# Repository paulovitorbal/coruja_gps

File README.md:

# coruja_gps — detector de radares embarcado

Projeto pessoal de estudo em sistemas embarcados: um alertador de radares e semáforos
sobre **Raspberry Pi Pico 2 W**, com firmware em **C++17 / Pico SDK**.

Lê telemetria de um GPS NEO-M8N por UART, confronta a posição com uma base local de
18.294 pontos e sinaliza em quatro zonas por display, LED RGB periférico e buzzer.

## Arquitetura

Quatro subsistemas, e o dado atravessa todos eles. Um CSV vira `radares.bin` na
estação de trabalho; o binário é publicado por um servidor mínimo; a configuração vai
para o cartão à mão; e o aparelho, ao clique, lê o cartão, busca a base pela rede e
**a grava de volta no cartão**.

Essa última parte é o RF05: *"baixá-la e salvá-la no cartão"*, com a troca atômica do
RF05.2 — baixa para `radares.tmp`, valida, renomeia a atual para `radares.bak` e só
então promove a nova. Queda de energia no meio de uma atualização não pode deixar o
aparelho sem base, porque a tela voltaria ao velocímetro normalmente e nada indicaria
a perda.

A cópia do `radares.bin` para o cartão à mão é só a **carga inicial**, e é opcional:
sem base o aparelho sobe, avisa, e o primeiro clique busca tudo pela rede.

No boot a base é lida **em fluxo** do cartão, decodificando direto no vetor de pontos.
Não é preferência de estilo: o arquivo tem 214 KB e o vetor ocupa 281 KB, e não existe
instante em que os dois caibam nos 181 KiB livres. Se o `radares.bin` não validar, o
firmware cai para o `radares.bak` — e avisa que está operando pela reserva.

**De onde vem o CSV é problema de quem monta** — o projeto não presume fonte nenhuma,
e por isso ela aparece no diagrama como uma nuvem anônima.

O que ainda não existe está tracejado e em cinza: gravar no cartão o que foi baixado,
o GPS, o display e o buzzer.

### Dentro do firmware

A divisão que mais importa é a **fronteira do hardware**. Em verde, o que compila e é
testado no host — validação de formato, decodificação de quadratura, verificação de
download, análise de URL. São 180 testes que rodam sem placa nenhuma, e é o que torna
possível trabalhar neste projeto enquanto um módulo não chegou pelo correio.

Em laranja, o que só existe no Pico. Esses módulos são finos de propósito: o
`ClienteHttp` entrega pedaços a quem chamou em vez de acumular, e quem verifica é o
`nucleo`.

### Como regerar os diagramas

As fontes são versionadas em `docs/*.puml`; os SVG são gerados.

```bash
plantuml -tsvg docs/arquitetura.puml docs/firmware.puml
```

## Base de pontos

O firmware carrega `radares.bin`, um binário compacto de 12 bytes por ponto,
ordenado por latitude. Ele é produzido por `converte.py` a partir de um CSV no
**padrão iGO8**:

```
X,Y,TYPE,SPEED,DirType,Direction
-44.021044,-19.799916,1,30,1,257
```

```bash
python3 converte.py base_igo8.txt radares.bin
```

**Outro formato de entrada?** Escreva seu próprio parser — e não reimplemente o
formato binário. `formato_radares.py` expõe as enumerações e o escritor:

```python
from formato_radares import Ponto, TipoPonto, Sentido, escreve

pontos = [Ponto(lat=-19.799916, lon=-44.021044, limite=30, rumo=257,
                tipo=TipoPonto.RADAR_FIXO, sentido=Sentido.UNIDIRECIONAL)]
escreve(pontos, "radares.bin")
```

O `escreve()` cuida de quantização, flags, **ordenação por latitude** e CRC-32 — as
quatro coisas que um parser erraria em silêncio. A ordenação é a pior: a busca
binária do firmware depende dela e erra *sem avisar* se faltar.

Para testar, `formato_radares.le()` relê com as mesmas validações do firmware: se
aceita, o firmware carrega. Use `converte.py` (padrão iGO8) como modelo.

Obter a base é problema de quem monta: o projeto não presume fonte nenhuma.

---

## Alimentação e instalação no veículo

Alimentado pelo **pós-chave**, derivado na caixa de fusíveis. **O que entra no aparelho
é 12 V** — o conversor CC ficou para dentro.

Essa topologia mudou em 2026-09-21, e o motivo foi o buzzer. Ver `docs/adr/0009`.

```
bateria ─ caixa de fusíveis ─ piggyback ─ fusível 2 A ─ 1,5 mm² trançado (12 V)
                                                               │
                                              ┌────────────────▼──────────────┐
                                              │  conector de entrada, 3 vias  │
                                              └────────────────┬──────────────┘
                                                               │  dentro do gabinete
                                     ┌─────────────────────────┼───────────────┐
                                     │                         │               │
                          ┌──────────▼──────────┐   ┌──────────▼─────────┐     │
                          │ TVS 24 V ┬ 470 µF   │   │ conversor 12 V→5 V │     │
                          │ (bidir.) │ 50 V     │   │ NÃO isolado, ≥40 V │     │
                          └──────────┴──────────┘   └──────────┬─────────┘     │
                                                               │ 5 V           │ 12 V
                                                    ┌──────────▼─────────┐  ┌──▼──────────┐
                                                    │ Schottky → VSYS 39 │  │ buzzer, 2 v.│
                                                    └────────────────────┘  └─────────────┘
```

Consumo: **~145 mA em 12 V** (≈1,6 W) em condução normal, com pico de ~200 mA quando a
tensão cai a 9 V durante a partida. No lado de 5 V são ~162 mA normais e ~310 mA no
pior caso sustentado.

### O buzzer é alimentado em 12 V

O **SFM-20B é especificado para 3–24 V**. Em 5 V ele opera perto do mínimo da faixa; em
12 V, perto do meio — e para um piezo ativo a pressão sonora sobe bastante com a
tensão. O **R-32** registra a audibilidade com janelas abertas a 80 km/h como a
incerteza que sobrou do projeto, e nenhuma mudança de firmware a resolve. Esta resolve,
ou pelo menos ataca a causa certa.

O circuito não muda: o `BC337` tem `Vceo` de 45 V, a corrente é a mesma, e o
acionamento pela base continua em 3,3 V através de 1 kΩ. Não há roda-livre a
acrescentar — o buzzer é piezoelétrico, carga capacitiva.

**O `D2` foi removido em 2026-09-25**, justamente por isso: em antiparalelo com carga
capacitiva ele fica reversamente polarizado nos dois estados e nunca conduz. Fecha o
R-16.

O retorno do buzzer não vai ao GND por fio — vai **pelo transistor**. É chaveamento
pelo lado baixo: `+12 V → buzzer → coletor`, `emissor → GND`. Com o `Q1` cortado o
coletor sobe a ~12 V pelo próprio buzzer, que é por que, lendo a netlist parada, as
duas pernas parecem estar no mesmo potencial.

### 🔴 O 12 V agora está dentro do gabinete

Essa é a contrapartida, e é séria.

Antes, com o conversor do lado de fora, nada acima de 5 V entrava na caixa. Agora
entram 12 V, e eles convivem a centímetros de um trilho cujo máximo absoluto é 5,5 V.
**12 V no nó `VSYS` destrói Pico, GPS, display e cartão juntos.**

Três consequências práticas:

* **O conector de entrada tem 3 vias e o do buzzer tem 2**, e isso voltou a ser medida
  de **segurança**, não de robustez. A revisão anterior deste documento dizia que
  trocá-los "deixou de ser destrutivo" — aquilo valia enquanto só havia 5 V; não vale
  mais.
* **O fio de 12 V não é vermelho.** A convenção antiga mandava vermelho para 5 V *e*
  12 V; duas tensões com a mesma cor a três centímetros uma da outra é convite a erro.
  No `.fzz` o 12 V é **amarelo**.
* **O fio do coletor também está em 12 V** sempre que o transistor está cortado, ou
  seja, na maior parte do tempo. Não é só o `+12 V` que precisa de cuidado.

### Proteção da entrada de 12 V

O fusível protege o **fio** contra curto; ele não reage a sobretensão. Daí o **TVS
bidirecional de 24 V** (`P6KE24CA` ou `1.5KE24CA`) e um **eletrolítico de 470 µF /
50 V** em paralelo na entrada. O clamp de 24 V cai numa janela estreita: tem de ficar
acima de 16 V, porque a rede é 13,8 a 14,4 V com o motor ligado, e abaixo de 40 V,
porque é o máximo do conversor. O `24CA` clampa em 33,2 V.

**O que isso não resolve:** um *load dump* real chega a 60–120 V por até 400 ms, o que
contra um clamp de 33 V significa mais de 1 kW sustentado — nenhum TVS axial pequeno
sobrevive. O que ele cobre são os transientes frequentes e de baixa energia, que são os
que matam módulo barato no uso diário. Para o load dump, o projeto se apoia em o
alternador de carro moderno já clampar internamente em ~35 V, e isso é **suposição, não
medição**.

Dois detalhes que estragam tudo se errados: o sufixo **`CA`** significa bidirecional, e
a versão `A` montada ao contrário fica em curto permanente; e o **fusível vai antes** da
proteção no percurso do cabo, porque o modo de falha desejável de um TVS é curto.

### Três decisões que não são óbvias

**Pós-chave em vez de bateria direta com relé.** O pós-chave permanece energizado
durante a partida, então não há reinício na ignição. O relé foi descartado porque a
bobina consome 80–150 mA contra ~180 mA do aparelho inteiro — gastaria quase tanto
quanto liga — e o benefício dele (consumo parasita zero) já vem da chave de ignição.

**Fusível de 2 A, não 10 A.** Fusível protege o fio, não a carga. Com 10 A, uma falta
intermediária de 6 A não abriria o fusível mas aqueceria o condutor. O cabo de 1,5 mm²
suporta ~15 A e está sobredimensionado de propósito — mas o fusível acompanha a carga.

**Conversor não isolado, com entrada ≥ 40 V.** As duas condições importam por motivos
diferentes. A entrada ampla é pelo *load dump*: 60–120 V por dezenas de milissegundos
quando a carga do alternador sai, e módulos comuns de 35 V podem não sobreviver. O
**não isolado** é pelo buzzer: sem continuidade entre o negativo de 12 V e o do
aparelho, a corrente do buzzer não fecha pelo emissor do `Q1` e ele simplesmente não
toca. Um conversor isolado — que parece melhor no anúncio — quebraria o circuito.

E há um mínimo tão importante quanto o máximo: **a entrada tem de aceitar ~9 V**,
porque é onde o trilho cai durante a partida. Módulo com mínimo de 12 V reinicia o
aparelho a cada vez que se dá a chave.

### Ajuste opcional da saída do conversor

O Schottky derruba 0,3–0,45 V, então 5,00 V na saída deixam o `VSYS` em ~4,6 V. Se o
módulo for ajustável, regule para **5,35–5,45 V** e o `VSYS` chega a ~5,0 V. **Nunca
acima de 5,8 V** — o `VSYS` aceita no máximo 5,5 V. Meça antes de conectar.

Com o buzzer em 12 V isso deixou de ser crítico: o que dependia de tensão nominal saiu
do trilho de 5 V.

### Conectores do aparelho

| Conector | Vias | Pino A | Pino B |
| :--- | :---: | :--- | :--- |
| Entrada (único) | **3** (central sem uso) | **+12 V** | GND |

Desde 2026-09-25 o **buzzer é soldado direto**, sem conector: os dois fios saem da
placa e vão ao SFM-27 no painel da caixa. Com isso o aparelho tem **um só conector
externo**, e o risco de trocar um pelo outro — que a contagem de vias apenas
administrava — deixa de existir. O preço é serviço: separar a tampa exige dessoldar.

## Documentos

Leia nesta ordem:

| Documento | O que é |
| :--- | :--- |
| **`requirements.md`** | Requisitos funcionais e não-funcionais, matriz de interação homem-máquina e fluxo de telas. É a especificação. |
| **`bom_schematic.md`** | Lista de materiais e roteamento pino a pino, com as pinagens físicas conferidas nas placas. |
| **`formato_dados.md`** | Formato binário `radares.bin`, estratégia de carga em RAM e busca geográfica em dois estágios. |
| **`revisao_tecnica.md`** | Revisão técnica com rastreabilidade: o que foi achado, decidido e o que segue aberto. |
| **`montagem.md`** | Montagem física na caixa Patola PB-111: chassi, fixação, prateleira do GPS, isolamento e passagem de cabos. |
| **`previa_host.md`** | O produto inteiro rodando no host contra o simulador: o que a primeira integração validou, o defeito que achou e o que ela ainda não exercita. |
| **`roteiro_bancada.html`** | Procedimento de medição para imprimir, com quadro de registro das leituras. |

## Estado

**Decidido:** C++17 com Pico SDK · GPS+GLONASS a 4 Hz (piso 3 Hz) · conector JST-XH ·
GPS alimentado em 5 V · Zona de Semáforo silenciosa · buzzer escalonado em 3 faixas ·
LED RGB exclusivo de estado de via.

**Pendente de bancada** — ver `roteiro_bancada.html`:

| Item | Medida |
| :--- | :--- |
| R-05 | Vf dos LEDs verde e azul, e calibração das razões R:G (amarelo) e R:B (rosa) |
| R-13 | Tensão do trilho 3V3 sob carga, com backlight em 100% |
| R-17 | Consumo do buzzer e pinagem do transistor |
| R-14 | Inspeção: regulador de 3 pinos na placa GPS — **sem ele, 5 V destroem o módulo** |

**Escopo futuro:** desenho de telas e interfaces visuais.

## Esquemático no Fritzing

`coruja_gps.fzz` foi **gerado** e depois **ajustado à mão** no Fritzing:

```bash
python3 gera_fritzing.py    # ⚠️ sobrescreve o .fzz e DESCARTA o ajuste manual
```

> ⚠️ **O `.fzz` versionado contém trabalho manual que o gerador não reproduz:**
> roteamento dos fios com pontos de dobra, orientação de 16 peças e 4 notas rotulando
> os módulos representados por headers genéricos. Regerar descarta tudo isso.
>
> O gerador é a fonte da **netlist**; o `.fzz` é a fonte do **layout**. Ao mudar a
> fiação, o caminho é editar `NETS`, regerar num arquivo temporário, comparar as redes
> e então aplicar a mudança à mão no Fritzing — não sobrescrever.
>
> **Sem divergências conhecidas** (2026-09-21). O `.fzz` foi regerado a partir da
> netlist atual e depois roteado à mão, fechando o **R-29**.
>
> O anterior tinha acumulado cinco atrasos, e o pior era silencioso: ele trazia o LED
> como **cátodo comum**, que se liga de forma oposta ao ânodo comum real (R-33). Quem
> montasse por ele teria um LED que não acende, sem pista do motivo. Os outros quatro
> eram os GPIO de vermelho e azul trocados (R-35), resistores de 68 Ω onde as medições
> pediam 470 e 150 (R-05), leitor SD com 8 pinos em vez de 9 (R-40) e o display como
> ST7789 240×240.
>
> A lição que fica: um `.fzz` editado à mão **não avisa quando envelhece**. A defesa
> aqui foi comparar netlists entre o gerado e o versionado — vale repetir isso antes de
> cada montagem, e não confiar na memória de quantas correções entraram desde a última
> vez. O documento de referência para montagem continua sendo o `bom_schematic.md`.

A netlist vive em `NETS`, dentro de `gera_fritzing.py`, transcrita do
`bom_schematic.md`. Mudou a fiação? Edite ali e regenere.

O `fritzing_geo.py` calcula a posição real de cada pino: lê o SVG de breadboard da
peça, resolve o mapeamento `connector → svgId` do `.fzp` e aplica os transforms de
grupo. Sem isso os fios sairiam desenhados fora dos pinos. A escala da cena
(90 unidades por polegada) foi medida empiricamente contra um sketch existente.

**Dependências do gerador:** Fritzing instalado (a biblioteca de peças é lida de
`/Applications/Fritzing.app`) e um sketch com a peça do Pico, de onde ela é
reaproveitada e embutida no `.fzz`.

Quatro módulos não têm peça na biblioteca — NEO-M8N, ST7789, leitor microSD e
KY-040 — e são representados por headers fêmea rotulados, com a contagem correta de
pinos. A peça de microSD que existe na biblioteca tem **zero conectores**, é
inutilizável.

Na vista protoboard há fios reais, coloridos por rede: **preto** = GND,
**vermelho** = 5 V, **azul** = 3V3, e cores distintas por grupo de sinal. Esquemático
e PCB usam conexões diretas, exibidas como ratsnest.

## Datasheets

| Arquivo | O que é |
| :--- | :--- |
| `NEO-M8_datasheet_UBX-15031086-R14.pdf` | Datasheet u-blox do módulo GPS, **revisão R14**. É a revisão citada em todas as análises deste projeto. |
| `NEO-M8_datasheet_UBX-15031086-R11.pdf` | Mesmo documento, **revisão R11** — anterior. Mantida para comparação; em caso de divergência, vale a R14. |
| `adafruit-microsd-spi-sdio.pdf` | Guia do breakout microSD. Fonte da polaridade do `DET` (cartão presente = ALTO, pull-up de 4,7 kΩ na placa) e da confirmação de que há pull-up em todos os pinos SPI. |

Valores extraídos do datasheet do GPS e usados no projeto: limites elétricos
(`VCC` 2,7–3,6 V, `VIN` 0–`VCC`, `IPIN` 10 mA), correntes (`ICCP` 67 mA, tracking
30 mA, `ICC_RF` até 50 mA), faixa térmica (−40 a +85 °C, **operação e
armazenamento**) e teto de taxa de navegação (**5 Hz** em GPS+GLONASS, 10 Hz em
GNSS único).

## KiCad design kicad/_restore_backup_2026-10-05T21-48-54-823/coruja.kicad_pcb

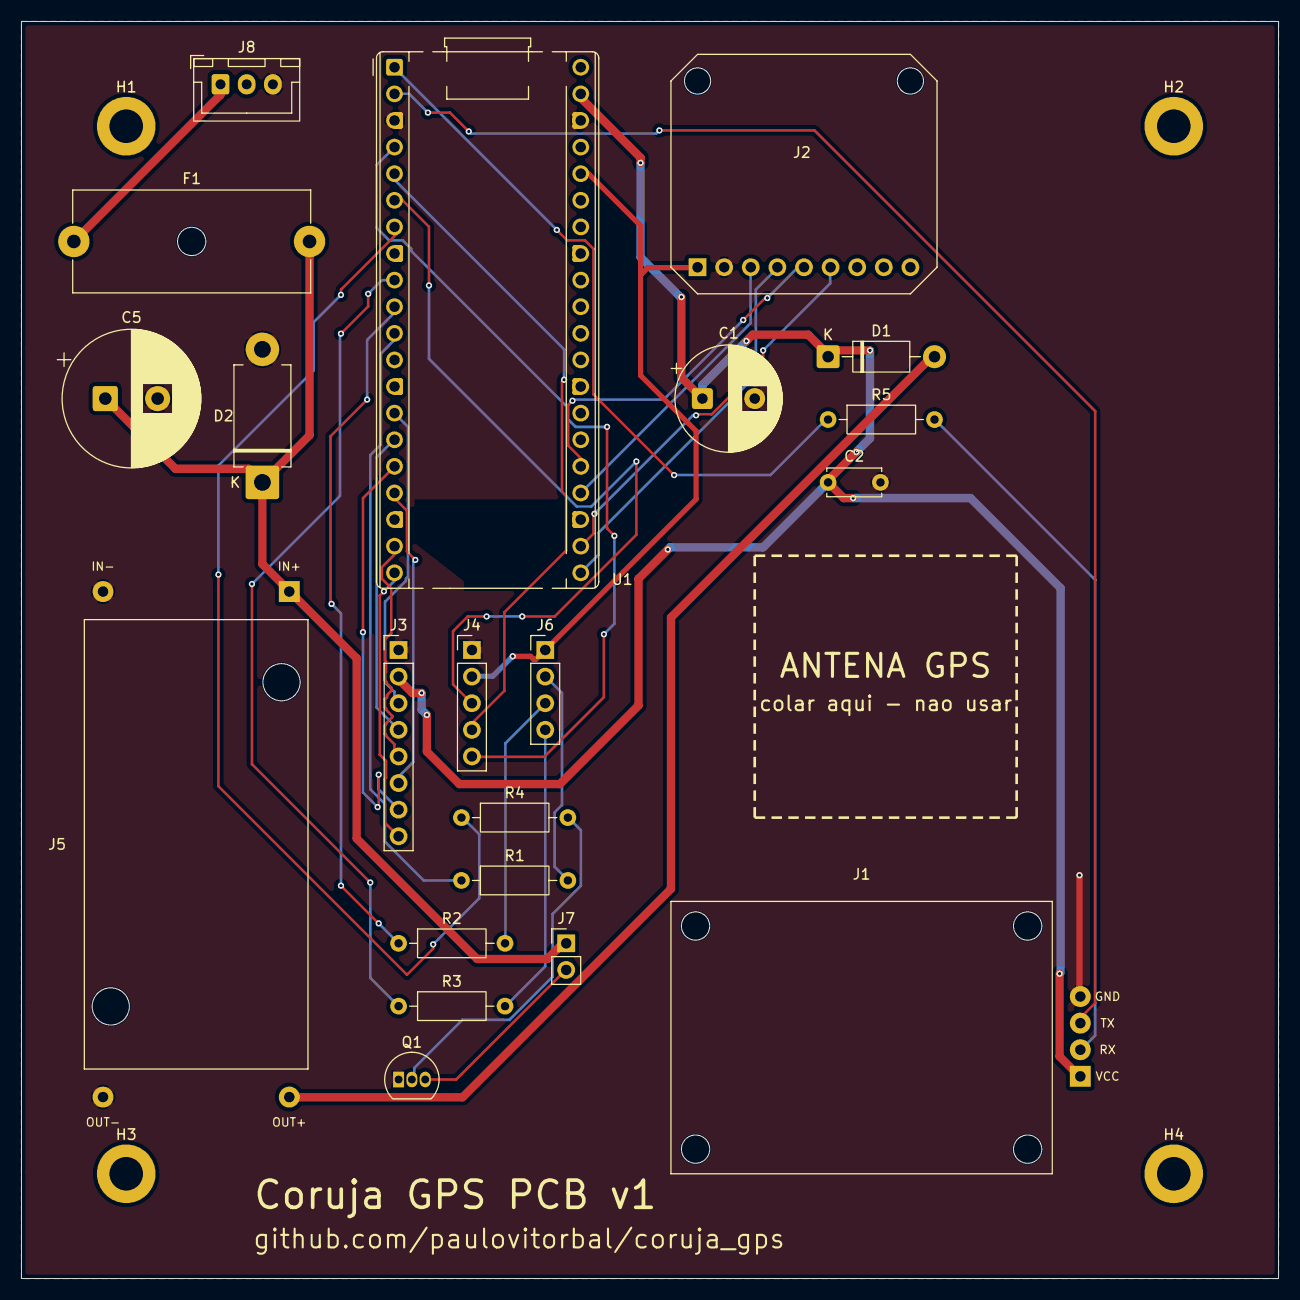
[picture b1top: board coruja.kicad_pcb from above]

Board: 2 copper layers, 120.0 x 120.0 mm, 25 parts (0 on the bottom side), 31 nets.

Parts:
C1: 470uF 25V 105C; CP_Radial_D10.0mm_P5.00mm
C2: 100nF; C_Disc_D5.0mm_W2.5mm_P5.00mm
C5: 470uF 50V 105C; CP_Radial_D13.0mm_P5.00mm
D1: 1N5817; D_DO-41_SOD81_P10.16mm_Horizontal
D2: P6KE24CA; D_DO-201AD_P12.70mm_Horizontal
F1: 2 A; Fuseholder_Cylinder-5x20mm_Schurter_0031_8201_Horizontal_Op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
H1: MountingHole_3.2mm_M3_DIN965_Pad
H2, H3, H4: MountingHole_3.2mm_M3_DIN965_Pad
J1: NEO-M8N (GY-GPS6MV2); GPS_GY_GPS6MV2
J2: Leitor microSD (9 pinos); Leitor_microSD_Adafruit4682
J3: Display; PinHeader_1x08_P2.54mm_Vertical
J4: Encoder; PinHeader_1x05_P2.54mm_Vertical
J5: Conversor_LM2596
J6: LED RGB; PinHeader_1x04_P2.54mm_Vertical
J7: BZ1 SFM-27; PinHeader_1x02_P2.54mm_Vertical
J8: +12v; JST_XH_B3B-XH-A_1x03_P2.50mm_Vertical
Q1: 2N2222; TO-92_Inline
R1: 330R (vermelho); R_Axial_DIN0207_L6.3mm_D2.5mm_P10.16mm_Horizontal
R2: 470R (verde); R_Axial_DIN0207_L6.3mm_D2.5mm_P10.16mm_Horizontal
R3: 150R (azul); R_Axial_DIN0207_L6.3mm_D2.5mm_P10.16mm_Horizontal
R4: 1k (base Q1); R_Axial_DIN0207_L6.3mm_D2.5mm_P10.16mm_Horizontal
R5: 1k; R_Axial_DIN0207_L6.3mm_D2.5mm_P10.16mm_Horizontal
U1: Pico 2W; RaspberryPi_Pico_Common_THT

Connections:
/3V3: J2.1, J4.2, J6.1, U1.36
/5V_CONV: D1.2, J5.3
/12V_ENTRADA: F1.1, J8.1
/12V_PROTEGIDO: C5.1, D2.1, F1.2, J5.1, J7.1
/BUZZ_BASE: Q1.2, R4.2
/BUZZ_COLETOR: J7.2, Q1.3
/BUZZ_GPIO5: R4.1, U1.7
/ENC_CLK: J4.5, U1.4
/ENC_DT: J4.4, U1.5
/ENC_SW: J4.3, U1.6
/GND: C1.2, C2.2, C5.2, D2.2, J1.4, J2.2, J3.1, J4.1, J5.2, J5.4, J8.3, Q1.1, U1.3, U1.38
/GPS_RX: J1.2, R5.2
/GPS_TX: J1.3, U1.2
/LED_B_CATODO: J6.4, R3.2
/LED_B_GPIO: R3.1, U1.9
/LED_G_CATODO: J6.3, R2.2
/LED_G_GPIO: R2.1, U1.10
/LED_R_CATODO: J6.2, R1.2
/LED_R_GPIO: R1.1, U1.11
/SD_CS: J2.6, U1.22
/SPI0_MISO: J2.4, U1.21
/SPI0_MOSI: J2.5, U1.25
/SPI0_SCK: J2.3, U1.24
/SPI1_MOSI: J3.4, U1.15
/SPI1_SCK: J3.3, U1.14
/TFT_BL_PWM: J3.8, U1.20
/TFT_CS: J3.7, U1.16
/TFT_DC: J3.6, U1.17
/TFT_RST: J3.5, U1.19
/UART_TX_R5: R5.1, U1.1
/VSYS_5V: C1.1, C2.1, D1.1, J1.1, J3.2, U1.39

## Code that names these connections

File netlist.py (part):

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    # ilegivel, e a chave do soquete nao abria por completo -- deixava o GPIO
    # 14 em 1,13 V, na zona indeterminada da logica de 3,3 V.
    #
    # ATENCAO: o GPIO 14 (pino 19) NAO esta mais livre -- virou o TFT_RST
    # abaixo. Se sobrar fiacao do soquete nesse pino, ela disputa o reset do
    # display e mantem o ST7789V em reset permanente.

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    #
    # Os resistores acompanham a COR, nao o GPIO: R1=330 no vermelho,
    # R2=470 no verde, R3=150 no azul.
    "LED_R_GPIO":   [("PICO", "11"), ("R1", "0")],   # GPIO 8
    "LED_R_CATODO": [("R1", "1"), ("LED", "R")],
    "LED_G_GPIO":   [("PICO", "10"), ("R2", "0")],   # GPIO 7
    "LED_G_CATODO": [("R2", "1"), ("LED", "G")],
    "LED_B_GPIO":   [("PICO", "9"), ("R3", "0")],    # GPIO 6
    "LED_B_CATODO": [("R3", "1"), ("LED", "B")],

    "BUZZ_GPIO5":   [("PICO", "7"), ("R4", "0")],
    "BUZZ_BASE":    [("R4", "1"), ("Q1", "B")],
    # O buzzer entra direto nas duas redes. Antes havia um conector no meio,
    # mas ele era passa-fio: nao mudava rede nenhuma, so acrescentava dois
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

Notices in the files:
parts and their libraries:
Adafruit 4682 microSD SPI/SDIO, 25.4 x 22.86 mm, barra de 9 pinos passo 2,54. Geometria do arquivo EAGLE da Adafruit (Limor Fried/Ladyada, CC-BY-SA), conferida contra a peca em 2026-10-05. A boca do cartao fica na borda oposta ao conector.
